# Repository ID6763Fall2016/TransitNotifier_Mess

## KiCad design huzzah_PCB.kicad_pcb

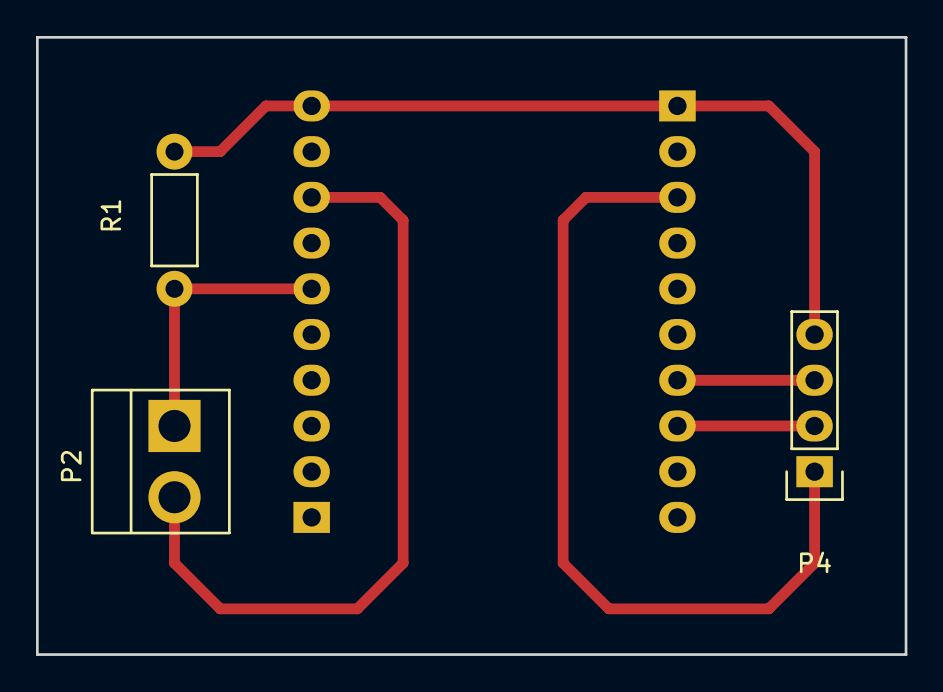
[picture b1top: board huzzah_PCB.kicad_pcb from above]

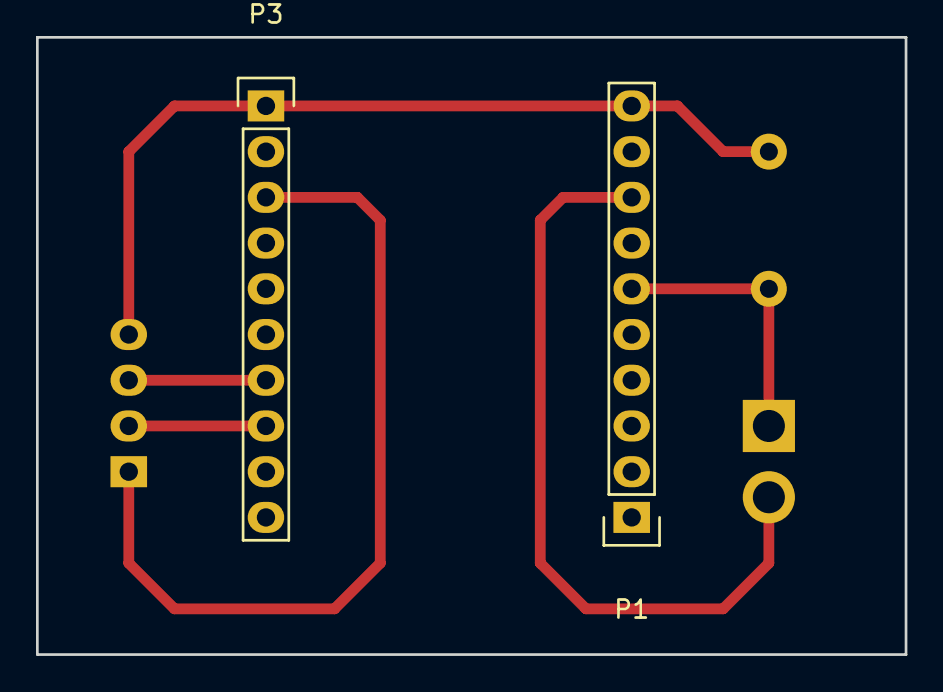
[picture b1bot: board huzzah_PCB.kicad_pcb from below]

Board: 2 copper layers, 48.3 x 34.3 mm, 5 parts (2 on the bottom side), 6 nets.

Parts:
P1, P3: CONN_01X10; Pin_Header_Straight_1x10
P2: CONN_01X02; Pin_Header_Straight_1x02_Pitch3.96mm_Friction_Lock
P4: CONN_01X04; Pin_Header_Straight_1x04
R1: R; Resistor_Horizontal_RM7mm

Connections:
BTN_READ: P1.6, P2.1, R1.1
CLOCK: P3.8, P4.2
DATA: P3.7, P4.3
GND: P1.10, P3.1, P4.4, R1.2
LED_V: P3.3, P4.1
V33: P1.8, P2.2

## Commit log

2016-10-25 push
2016-11-02 KiCAD files
